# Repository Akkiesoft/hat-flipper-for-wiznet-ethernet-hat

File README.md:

# HAT Flipper for WIZnet Ethernet HAT

WIZnet Ethernet HATの向きを180度回転させて、PicoのMicroUSBコネクターとRJ-45の口の向きを揃えるためのアダプターボードです。また、Ethernet HAT配線をSPI0からSPI1に変更して、被りがちなピン配置を回避します。

おまけとして、Picoのリセットボタン用回路を実装しています。TSB001タクタイルスイッチを使用して実装可能です。

| 役割 | EthernetHAT(SPI0) | 変換基板(SPI1) |
| ---- | ----------------- | -------------- |
| MISO | GP16              | GP12           |
| CSn  | GP17              | GP9            |
| SCLK | GP18              | GP10           |
| MOSI | GP19              | GP11           |
| RSTn | GP20              | GP15           |
| INTn | GP21              | GP14           |

## 解説

https://akkiesoft.hatenablog.jp/entry/20240819/1724048755

## License

MIT License

2024 @Akkiesoft

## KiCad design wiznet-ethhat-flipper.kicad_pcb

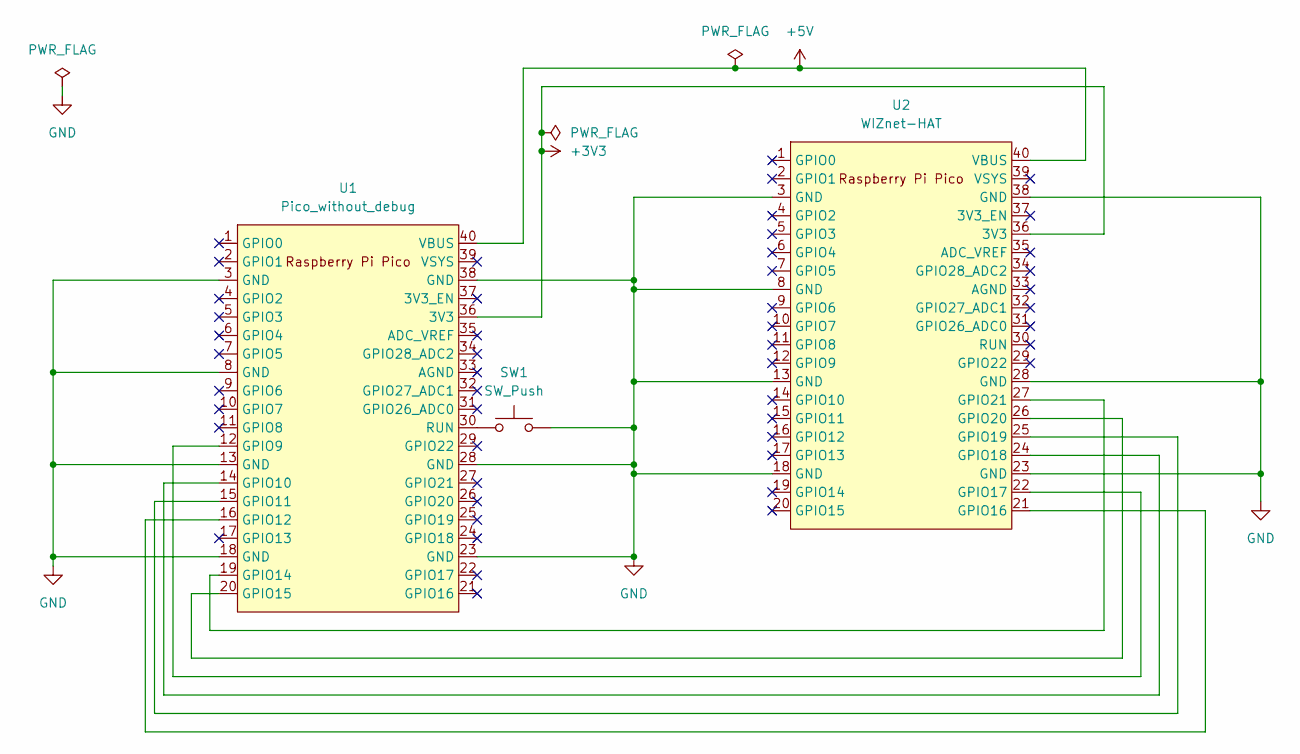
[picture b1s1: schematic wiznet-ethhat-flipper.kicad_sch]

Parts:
SW1: SW_Push; SW_TSB001
U1: Pico_without_debug; RPi_Pico_Skel
U2: WIZnet-HAT; RPi_Pico_Skel

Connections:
+3V3: U1.36 (3V3), U2.36 (3V3)
+5V: U1.40 (VBUS), U2.40 (VBUS)
GND: SW1.2, U1.3 (GND), U1.8 (GND), U1.13 (GND), U1.18 (GND), U1.23 (GND), U1.28 (GND), U1.38 (GND), U2.3 (GND), U2.8 (GND), U2.13 (GND), U2.18 (GND), U2.23 (GND), U2.28 (GND), U2.38 (GND)
unnamed: SW1.1, U1.30 (RUN)
unnamed: U1.12 (GPIO9), U2.22 (GPIO17)
unnamed: U1.14 (GPIO10), U2.24 (GPIO18)
unnamed: U1.15 (GPIO11), U2.25 (GPIO19)
unnamed: U1.16 (GPIO12), U2.21 (GPIO16)
unnamed: U1.19 (GPIO14), U2.27 (GPIO21)
unnamed: U1.20 (GPIO15), U2.26 (GPIO20)

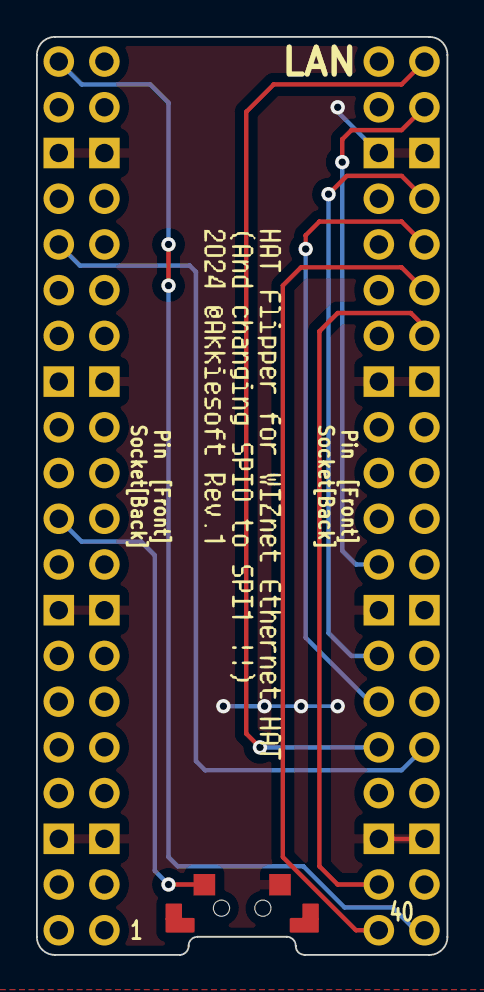
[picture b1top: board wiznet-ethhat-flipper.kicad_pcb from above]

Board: 2 copper layers, 22.8 x 51.0 mm, 3 parts (0 on the bottom side), 10 nets.

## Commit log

2024-08-19 init
2024-12-06 add readme
